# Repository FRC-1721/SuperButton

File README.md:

# Welcome!

# Getting Started!

Clone the repo with submodules!

```shell
git clone --recurse-submodules https://github.com/FRC-1721/SuperButton.git
```

## Init Submodules

Some libraries and resources are included as submodules, run the following
command to initialize them before opening the main sch

(If you get a missing library error, make sure to do this)

```shell
git submodule update --init --recursive
```

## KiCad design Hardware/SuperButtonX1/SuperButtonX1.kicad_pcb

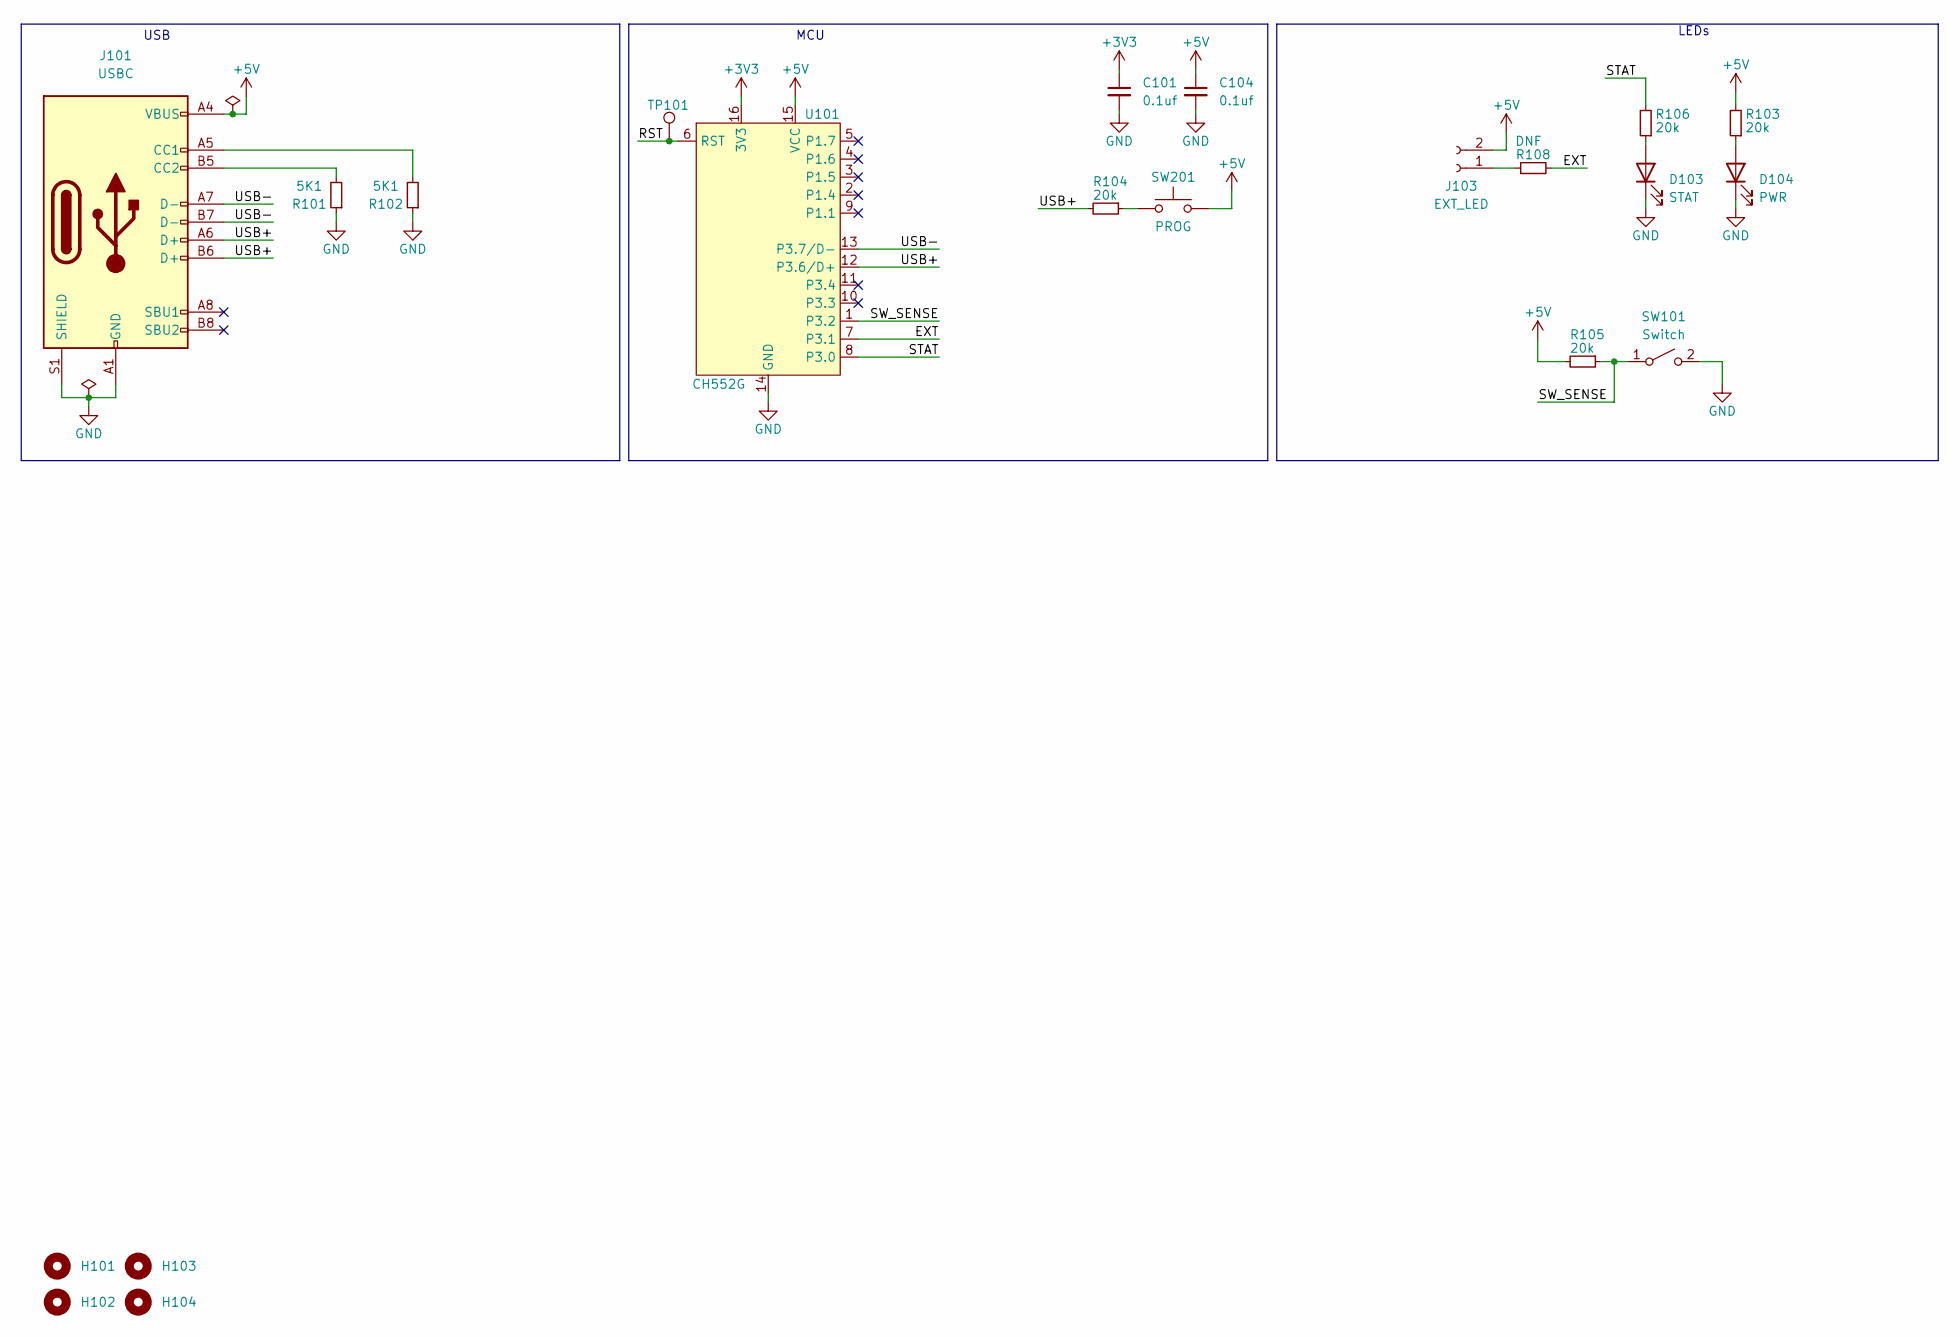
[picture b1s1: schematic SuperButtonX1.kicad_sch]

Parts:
C101, C104: 0.1uf; C_0805_2012Metric; LCSC# C49678
D103: STAT; LED_0805_2012Metric; LCSC# C84256
D104: PWR; LED_0805_2012Metric; LCSC# C84256
H101, H102, H103, H104: MountingHole; MountingHole_6.5mm
J101: USBC; USB_C_Receptacle_XKB_U262-16XN-4BVC11; LCSC# C319148
J103: EXT_LED; SolderWire-0.15sqmm_1x02_P4mm_D0.5mm_OD1.5mm_Relief
R101, R102: 5K1; R_0805_2012Metric; LCSC# C269748
R103, R104, R105, R106: 20k; R_0805_2012Metric; LCSC# C17606
R108: DNF; R_0805_2012Metric; LCSC# C17606
SW101: Switch; SW_Cherry_MX_PCB
SW201: PROG; SW_SPST_TL3342; LCSC# C318884
TP101: TestPoint; TestPoint_Pad_2.5x2.5mm
U101: CH552G; SOP-16_3.9x9.9mm_P1.27mm; LCSC# C111292

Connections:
+3V3: C101.1, U101.16 (3V3)
+5V: C104.1, J101.A4 (VBUS), J101.A9 (VBUS), J101.B4 (VBUS), J101.B9 (VBUS), J103.2, R103.2, R105.2, U101.15 (VCC); also elsewhere on the board
/EXT: R108.2, U101.7 (P3.1)
/RST: TP101.1, U101.6 (RST)
/STAT: R106.2, U101.8 (P3.0)
/SW_SENSE: R105.1, SW101.1 (A), U101.1 (P3.2)
/USB+: J101.A6 (D+), J101.B6 (D+), R104.2, U101.12 (P3.6/D+)
/USB-: J101.A7 (D-), J101.B7 (D-), U101.13 (P3.7/D-)
GND: C101.2, C104.2, D103.1 (K), D104.1 (K), J101.A1 (GND), J101.A12 (GND), J101.B1 (GND), J101.B12 (GND), J101.S1 (SHIELD), R101.1, R102.1, SW101.2 (B), U101.14 (GND)
unnamed: D103.2 (A), R106.1
unnamed: D104.2 (A), R103.1
unnamed: J101.A5 (CC1), R102.2
unnamed: J101.B5 (CC2), R101.2
unnamed: J103.1, R108.1
unnamed 14: R104.1; also elsewhere on the board

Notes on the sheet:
USB
LEDs
MCU

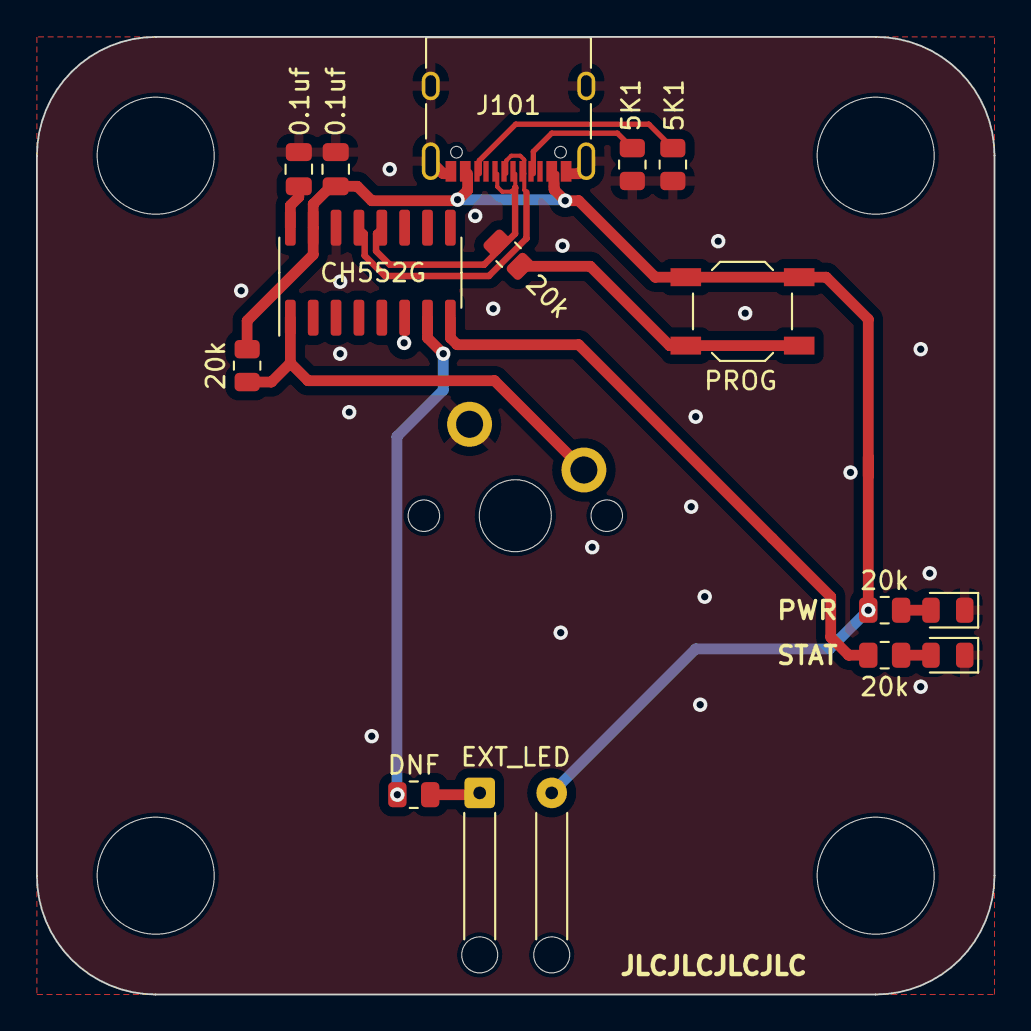
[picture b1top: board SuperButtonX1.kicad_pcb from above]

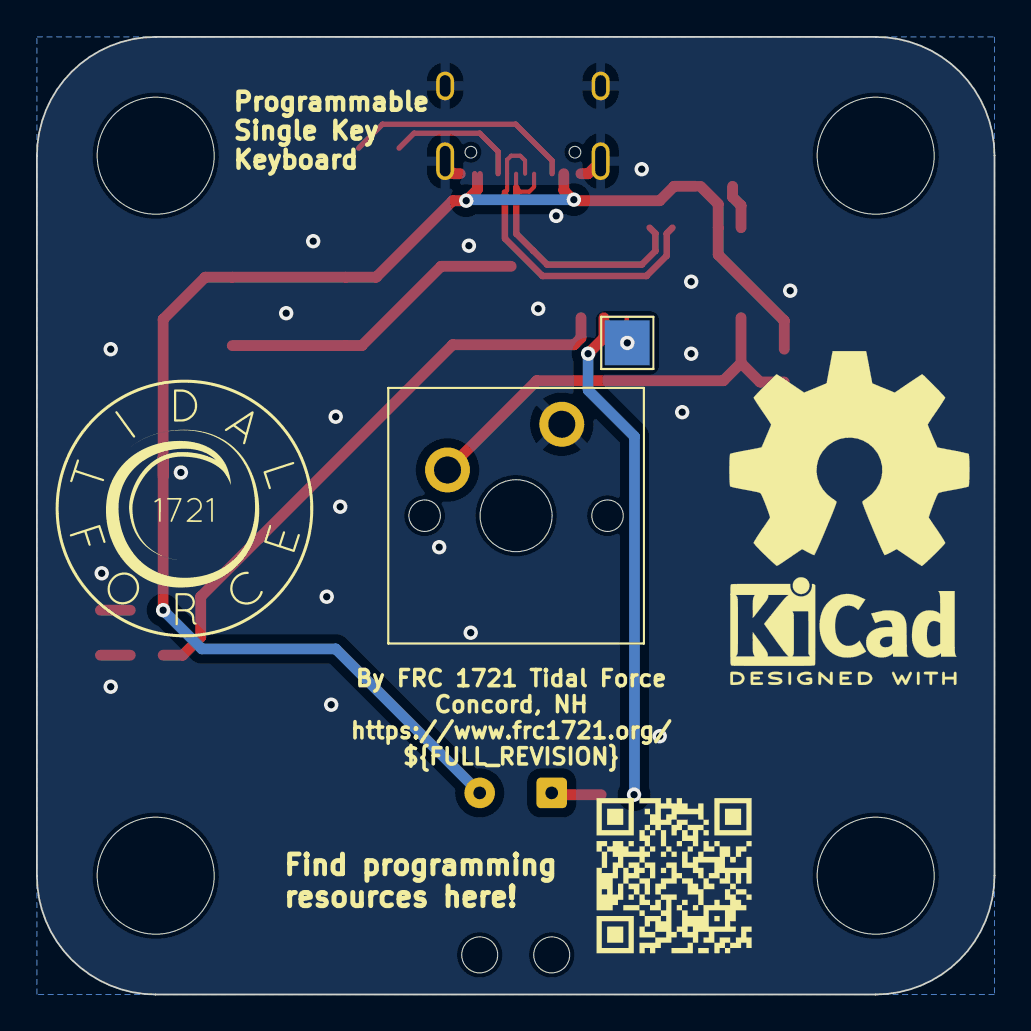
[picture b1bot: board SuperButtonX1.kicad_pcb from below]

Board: 2 copper layers, 53.2 x 53.2 mm, 21 parts (6 on the bottom side), 15 nets.

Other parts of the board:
SW102: PROG; SW_SPST_TL3342

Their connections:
+5V: SW102.2; also elsewhere on the board
unnamed 14: SW102.1; also elsewhere on the board

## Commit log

2023-01-18 Blank project!
2023-01-18 Add switches
2023-01-18 Add board outline
2023-01-19 Add ci/cd
2023-01-19 Add reset pullups
2023-01-19 Fix firmware
2023-01-19 Fork firmware to atmega8
2023-01-20 Come back to this later
2023-05-17 Finalize inital button design
2023-05-17 fixups
2023-05-17 Do not run ERC
2023-05-17 Bump kibot to 7
2023-05-17 fixup! Bump kibot to 7
2023-05-17 Fix test pad
2023-05-17 Cleanup silk
2023-05-17 CH552G (#3)
2023-05-17 Add space for multiple variants
2023-05-17 Add blank X3 button clone
2023-05-17 is it valid to submit all pngs?
2023-05-17 Bump
2023-05-17 matrixify
2023-05-17 Fix variants workflows (#5)
2023-05-17 Include LCSC part numbers in BOM
2023-05-17 include csv in staging
2023-05-17 Bump readme
2023-05-17 Swap out
2023-05-17 Enforce submodules
2023-05-17 Clean up Super Button X1
2023-05-17 Prettyify
2023-05-17 What a mess
2023-05-17 need to solve compiling usb HID lib
2023-05-17 Return to PIO
2023-05-17 increased width of board, moved a couple of the components around to help better fit the wiring for the two new buttons, not finished yet.
2023-05-17 Clean up x3 board
2023-05-17 I don't like how this is routed, but I thought I'd leave it at this for now, I would like to move a couple of things around for the sake of easier routing
2023-05-19 Fix routing
2023-05-22 Fix Jack's name
2023-05-22 Feat/Variants (#4)
2023-06-23 pause here
2023-06-23 Add JLCJLCJLC to boards
2023-08-22 add single board top
